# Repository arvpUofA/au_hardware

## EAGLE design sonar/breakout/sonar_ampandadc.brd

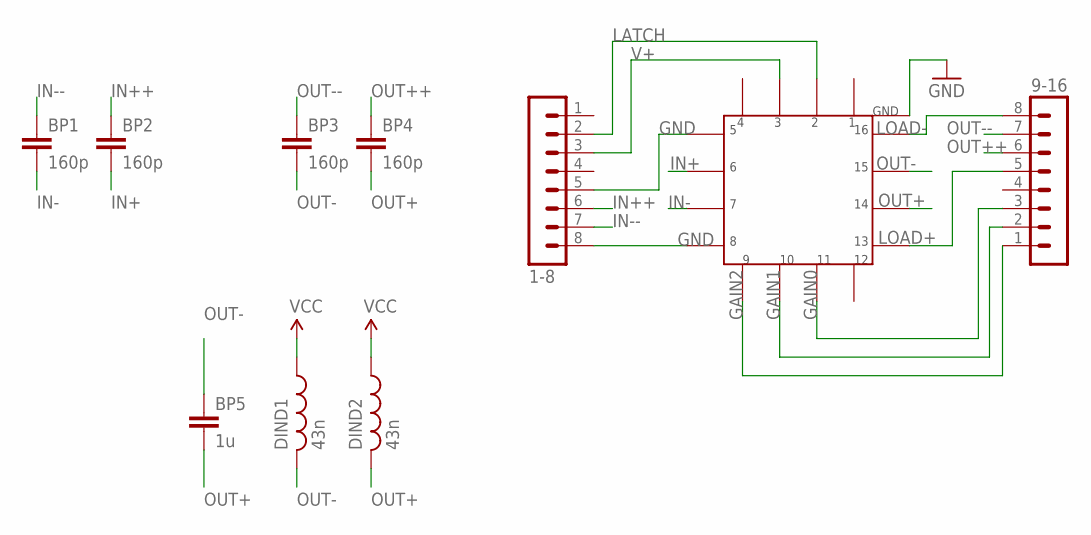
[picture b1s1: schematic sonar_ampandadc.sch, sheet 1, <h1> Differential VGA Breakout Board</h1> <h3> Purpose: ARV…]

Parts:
1-8, 9-16: MA08-1
BP1, BP2, BP3, BP4: 160p; 0603-CAP
BP5: 1u; 0603-CAP
DIND1, DIND2: 43n; 0402-RES
U$1: LMH6514; WQFN4X4

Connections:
GAIN0: 9-16.3, U$1.P$11
GAIN1: 9-16.2, U$1.P$10
GAIN2: 9-16.1, U$1.P$9
GND: 1-8.5, 1-8.8, U$1.GND, U$1.P$5, U$1.P$8; also elsewhere on the board
IN+: BP2.2, U$1.P$6
IN++: 1-8.6, BP2.1
IN-: BP1.2, U$1.P$7
IN--: 1-8.7, BP1.1
LATCH: 1-8.2, U$1.P$2
LOAD+: 9-16.5, U$1.P$13; also elsewhere on the board
LOAD-: 9-16.8, U$1.P$16; also elsewhere on the board
OUT+: BP4.2, BP5.2, DIND2.2, U$1.P$14
OUT++: 9-16.6, BP4.1; also elsewhere on the board
OUT-: BP3.2, BP5.1, DIND1.2, U$1.P$15
OUT--: 9-16.7, BP3.1; also elsewhere on the board
V+: 1-8.3, DIND1.1, DIND2.1, U$1.P$3; also elsewhere on the board

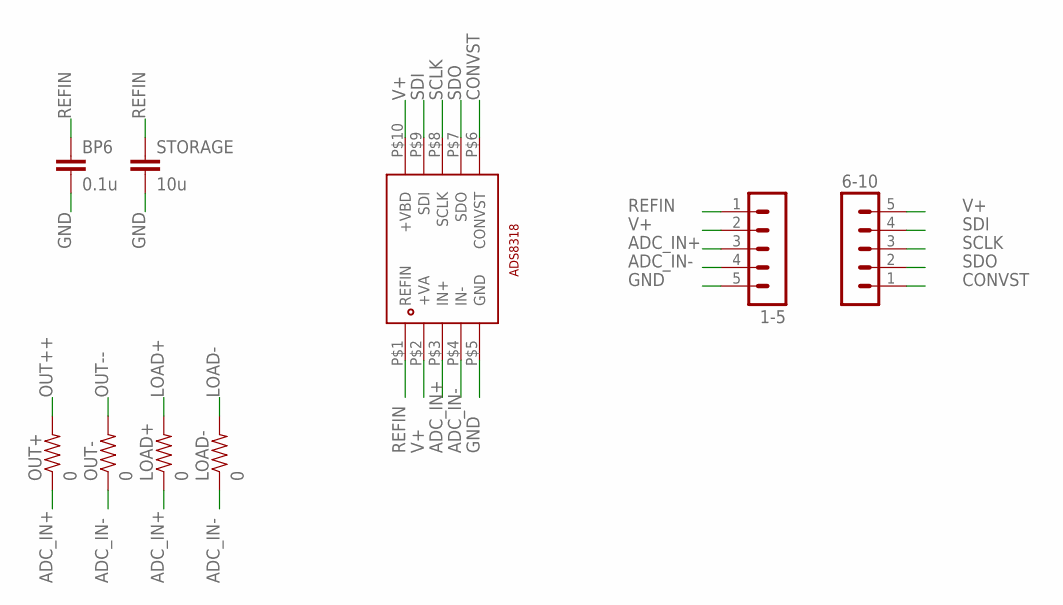
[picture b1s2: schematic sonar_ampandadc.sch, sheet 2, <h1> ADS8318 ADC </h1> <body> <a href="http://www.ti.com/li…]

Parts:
1-5, 6-10: MA05-1
BP6: 0.1u; 0603-CAP
LOAD+: 0; 0603-RES
LOAD-: 0; 0603-RES
OUT+: 0; 0603-RES
OUT-: 0; 0603-RES
STORAGE: 10u; 0603-CAP
U$2: ADS8318; 10-VSSOP

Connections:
ADC_IN+: 1-5.3, LOAD+.1, OUT+.1, U$2.P$3 (IN+)
ADC_IN-: 1-5.4, LOAD-.1, OUT-.1, U$2.P$4 (IN-)
CONVST: 6-10.1, U$2.P$6 (CONVST)
GND: 1-5.5, BP6.2, STORAGE.2, U$2.P$5 (GND); also elsewhere on the board
LOAD+: LOAD+.2; also elsewhere on the board
LOAD-: LOAD-.2; also elsewhere on the board
OUT++: OUT+.2; also elsewhere on the board
OUT--: OUT-.2; also elsewhere on the board
REFIN: 1-5.1, BP6.1, STORAGE.1, U$2.P$1 (REFIN)
SCLK: 6-10.3, U$2.P$8 (SCLK)
SDI: 6-10.4, U$2.P$9 (SDI)
SDO: 6-10.2, U$2.P$7 (SDO)
V+: 1-5.2, 6-10.5, U$2.P$2 (+VA), U$2.P$10 (+VBD); also elsewhere on the board

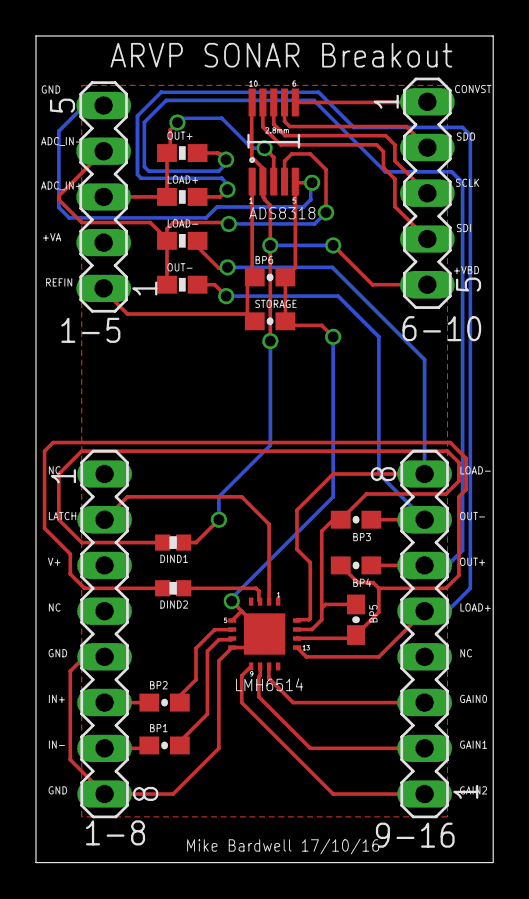
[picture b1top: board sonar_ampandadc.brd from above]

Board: 2 copper layers, 25.4 x 45.9 mm, 19 parts (0 on the bottom side), 23 nets.

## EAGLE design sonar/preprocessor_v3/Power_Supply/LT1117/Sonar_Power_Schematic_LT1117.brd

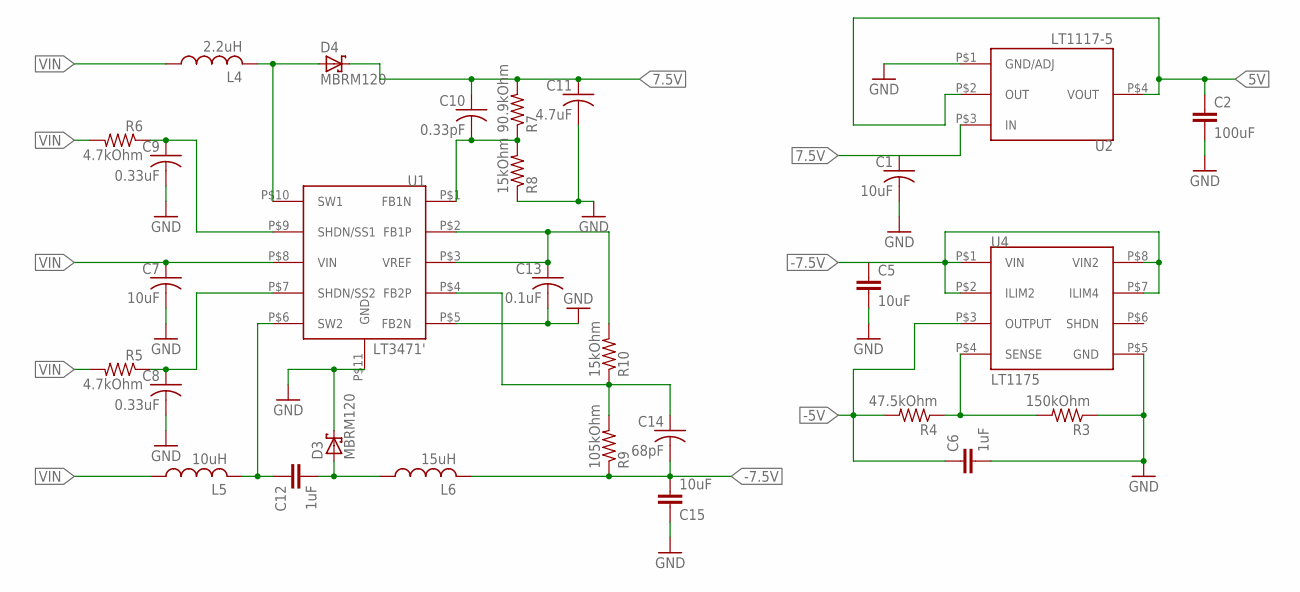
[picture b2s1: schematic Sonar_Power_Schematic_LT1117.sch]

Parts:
C1, C5, C7, C15: 10uF; C0603
C2: 100uF; C1210
C6, C12: 1uF; C1206
C8, C9: 0.33uF; C0603
C10: 0.33pF; C0603
C11: 4.7uF; C0603
C13: 0.1uF; C0603
C14: 68pF; C0603
D3, D4: MBRM120; DO-216AA
L4: 2.2uH; NS4.9X4.9
L5: 10uH; NS5X5
L6: 15uH; NS5X5
R3: 150kOhm; R0603
R4: 47.5kOhm; R0603
R5, R6: 4.7kOhm; R0603
R7: 90.9kOhm; R0603
R8, R10: 15kOhm; R0603
R9: 105kOhm; R0603
U1: LT3471'; 10-WFDFN
U2: LT1117-5; SOT233-3
U4: LT1175; 8-SOIC

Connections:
5V: C2.1, U2.P$2 (OUT), U2.P$4 (VOUT)
7.5V: C1.1, C10.1, C11.1, D4.P$1 (C), R7.2, U2.P$3 (IN)
-5V: C6.1, R4.2, U4.P$3 (OUTPUT)
-7.5V: C5.1, C14.2, C15.2, L6.P$2 (2), R9.1, U4.P$1 (VIN), U4.P$2 (ILIM2), U4.P$7 (ILIM4), U4.P$8 (VIN2)
GND: C1.2, C2.2, C5.2, C6.2, C7.2, C8.2, C9.2, C11.2, C13.2, C15.1, D3.P$1 (C), R3.1, R8.1, U1.P$5 (FB2N), U1.P$11 (GND), U2.P$1 (GND/ADJ), U4.P$5 (GND)
unnamed: R3.2, R4.1, U4.P$4 (SENSE)
unnamed: D4.P$2 (A), L4.P$2 (2), U1.P$10 (SW1)
unnamed: C10.2, R7.1, R8.2, U1.P$1 (FB1N)
unnamed: C12.1, L5.P$2 (2), U1.P$6 (SW2)
unnamed: C12.2, D3.P$2 (A), L6.P$1 (1)
unnamed: C14.1, R9.2, R10.1, U1.P$4 (FB2P)
SS1: C9.1, R6.1, U1.P$9 (SHDN/SS1)
SS2: C8.1, R5.1, U1.P$7 (SHDN/SS2)
VIN: C7.1, L4.P$1 (1), L5.P$1 (1), R5.2, R6.2, U1.P$8 (VIN)
VREF: C13.1, R10.2, U1.P$2 (FB1P), U1.P$3 (VREF)

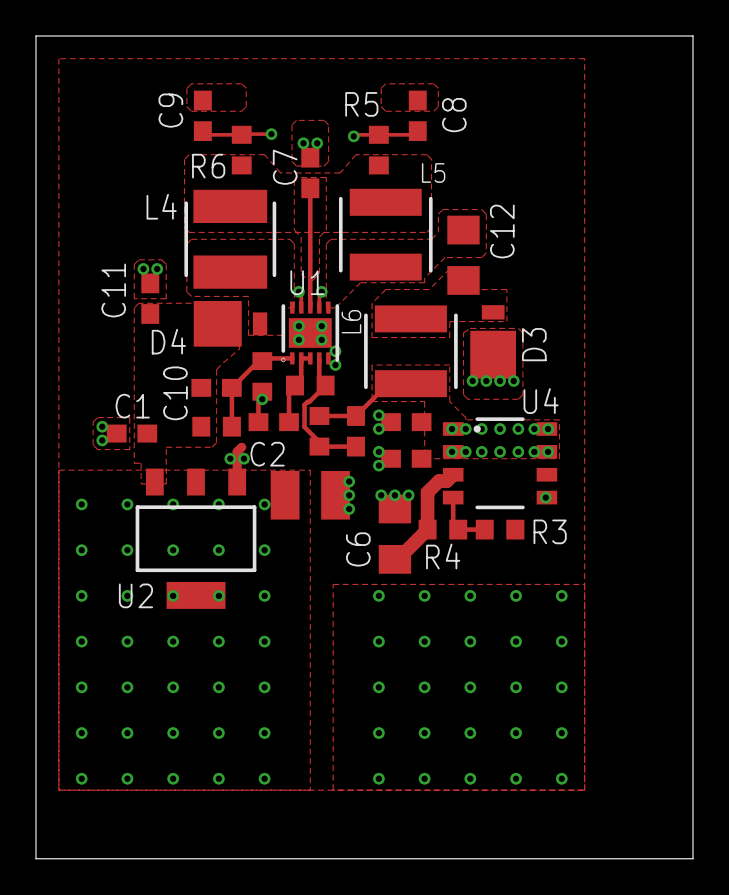
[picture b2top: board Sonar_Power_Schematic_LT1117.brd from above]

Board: 4 copper layers, 36.5 x 45.7 mm, 29 parts (0 on the bottom side), 15 nets.

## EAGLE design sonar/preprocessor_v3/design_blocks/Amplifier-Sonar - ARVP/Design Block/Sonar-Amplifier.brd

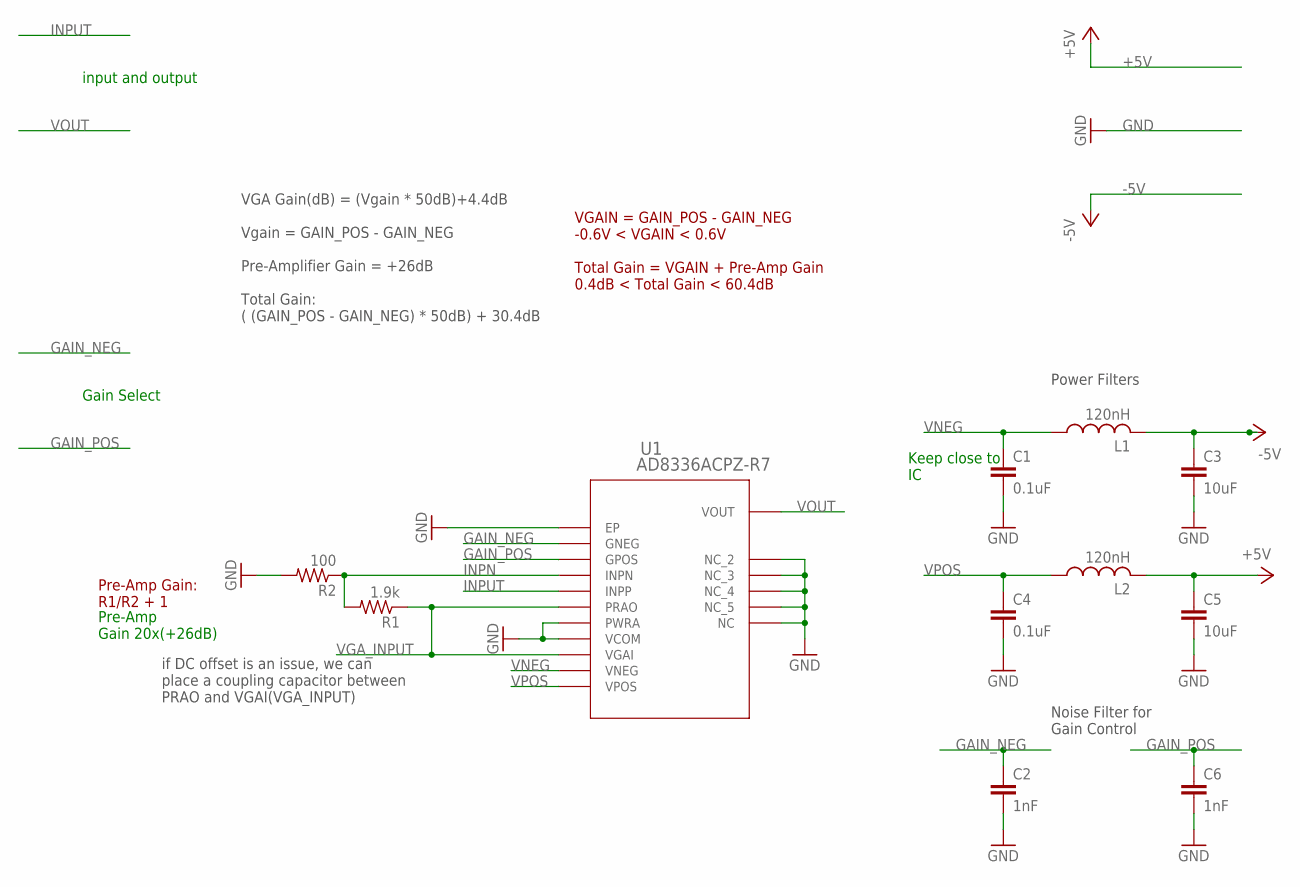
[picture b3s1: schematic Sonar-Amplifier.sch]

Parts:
C1, C4: 0.1uF; C0603
C2, C6: 1nF; C0603
C3, C5: 10uF; C1206
L1, L2: 120nH; L3225P
R1: 1.9k; R0603
R2: 100; R0603
U1: AD8336ACPZ-R7; CP_16_4

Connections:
+5V: C5.1, L2.2
-5V: C3.1, L1.2
GAIN_NEG: C2.1, U1.GNEG
GAIN_POS: C6.1, U1.GPOS
GND: C1.2, C2.2, C3.2, C4.2, C5.2, C6.2, R2.2, U1.GND1 (EP), U1.NC, U1.NC1 (NC_2), U1.NC2 (NC_3), U1.NC3 (NC_4), U1.NC4 (NC_5), U1.PWRA, U1.VCOM
INPN: R1.2, R2.1, U1.INPN
INPUT: U1.INPP
VGA_INPUT: R1.1, U1.PRAO, U1.VGAI
VNEG: C1.1, L1.1, U1.VNEG
VOUT: U1.VOUT
VPOS: C4.1, L2.1, U1.VPOS

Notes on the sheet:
Pre-Amp Gain 20x(+26dB)
Power Filters
Keep close to IC
Noise Filter for Gain Control
input and output
Pre-Amp Gain: R1/R2 + 1
if DC offset is an issue, we can place a coupling capacitor between PRAO and VGAI(VGA_INPUT)
Gain Select
VGA Gain(dB) = (Vgain * 50dB)+4.4dB Vgain = GAIN_POS - GAIN_NEG Pre-Amplifier Gain = +26dB Total Gain: ( (GAIN_POS - GAIN_NEG) * 50dB) + 30.4dB
VGAIN = GAIN_POS - GAIN_NEG -0.6V < VGAIN < 0.6V Total Gain = VGAIN + Pre-Amp Gain 0.4dB < Total Gain < 60.4dB

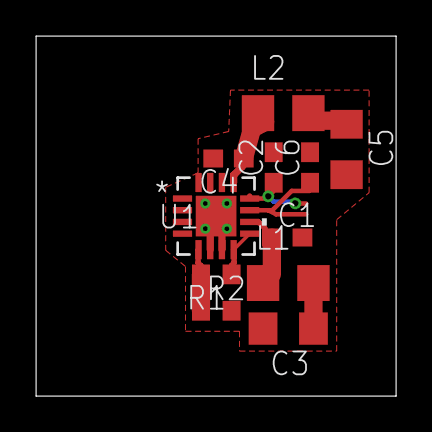
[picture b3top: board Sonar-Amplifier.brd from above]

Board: 4 copper layers, 20.0 x 20.0 mm, 11 parts (0 on the bottom side), 9 nets.

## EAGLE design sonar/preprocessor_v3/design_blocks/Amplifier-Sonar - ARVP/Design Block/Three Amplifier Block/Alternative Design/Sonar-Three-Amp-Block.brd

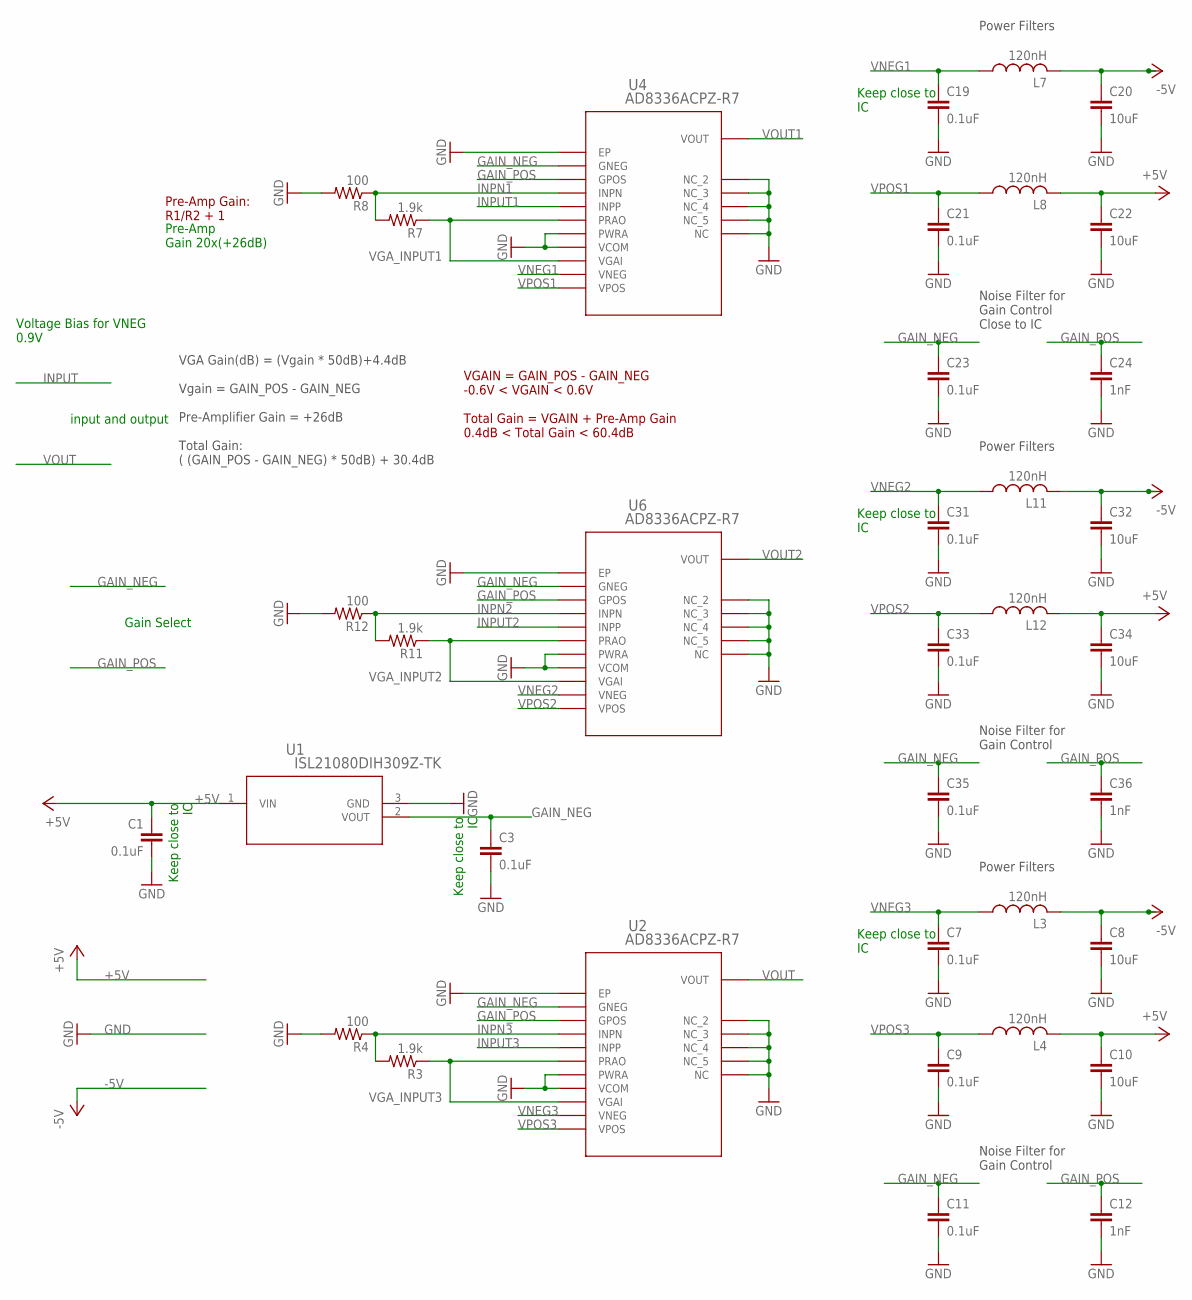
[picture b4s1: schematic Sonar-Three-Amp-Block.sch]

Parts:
C1, C3, C7, C9, C11, C19, C21, C23, C31, C33, C35: 0.1uF; C0603
C8, C10, C20, C22, C32, C34: 10uF; C1206
C12, C24, C36: 1nF; C0603
L3, L4, L7, L8, L11, L12: 120nH; L3225P
R3, R7, R11: 1.9k; R0603
R4, R8, R12: 100; R0603
U1: ISL21080DIH309Z-TK; P3_064
U2, U4, U6: AD8336ACPZ-R7; CP_16_4

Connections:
+5V: C1.1, C10.1, C22.1, C34.1, L4.2, L8.2, L12.2, U1.1 (VIN)
-5V: C8.1, C20.1, C32.1, L3.2, L7.2, L11.2
GAIN_NEG: C3.1, C11.1, C23.1, C35.1, U1.2 (VOUT), U2.GNEG, U4.GNEG, U6.GNEG
GAIN_POS: C12.1, C24.1, C36.1, U2.GPOS, U4.GPOS, U6.GPOS
GND: C1.2, C3.2, C7.2, C8.2, C9.2, C10.2, C11.2, C12.2, C19.2, C20.2, C21.2, C22.2, C23.2, C24.2, C31.2, C32.2, C33.2, C34.2, C35.2, C36.2, R4.2, R8.2, R12.2, U1.3 (GND), U2.GND1 (EP), U2.NC, U2.NC1 (NC_2), U2.NC2 (NC_3), U2.NC3 (NC_4), U2.NC4 (NC_5), U2.PWRA, U2.VCOM, U4.GND1 (EP), U4.NC, U4.NC1 (NC_2), U4.NC2 (NC_3), U4.NC3 (NC_4), U4.NC4 (NC_5), U4.PWRA, U4.VCOM, U6.GND1 (EP), U6.NC, U6.NC1 (NC_2), U6.NC2 (NC_3), U6.NC3 (NC_4), U6.NC4 (NC_5), U6.PWRA, U6.VCOM
INPN1: R7.2, R8.1, U4.INPN
INPN2: R11.2, R12.1, U6.INPN
INPN3: R3.2, R4.1, U2.INPN
INPUT1: U4.INPP
INPUT2: U6.INPP
INPUT3: U2.INPP
VGA_INPUT1: R7.1, U4.PRAO, U4.VGAI
VGA_INPUT2: R11.1, U6.PRAO, U6.VGAI
VGA_INPUT3: R3.1, U2.PRAO, U2.VGAI
VNEG1: C19.1, L7.1, U4.VNEG
VNEG2: C31.1, L11.1, U6.VNEG
VNEG3: C7.1, L3.1, U2.VNEG
VOUT: U2.VOUT
VOUT1: U4.VOUT
VOUT2: U6.VOUT
VPOS1: C21.1, L8.1, U4.VPOS
VPOS2: C33.1, L12.1, U6.VPOS
VPOS3: C9.1, L4.1, U2.VPOS

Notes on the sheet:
Pre-Amp Gain 20x(+26dB)
Power Filters
Keep close to IC
Noise Filter for Gain Control Close to IC
input and output
Pre-Amp Gain: R1/R2 + 1
Gain Select
VGA Gain(dB) = (Vgain * 50dB)+4.4dB Vgain = GAIN_POS - GAIN_NEG Pre-Amplifier Gain = +26dB Total Gain: ( (GAIN_POS - GAIN_NEG) * 50dB) + 30.4dB
VGAIN = GAIN_POS - GAIN_NEG -0.6V < VGAIN < 0.6V Total Gain = VGAIN + Pre-Amp Gain 0.4dB < Total Gain < 60.4dB
Noise Filter for Gain Control
Voltage Bias for VNEG 0.9V

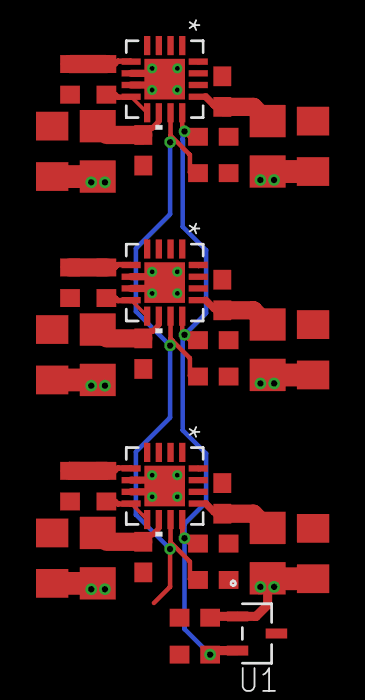
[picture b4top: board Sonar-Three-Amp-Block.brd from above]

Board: 4 copper layers, 36 parts (0 on the bottom side), 17 nets.

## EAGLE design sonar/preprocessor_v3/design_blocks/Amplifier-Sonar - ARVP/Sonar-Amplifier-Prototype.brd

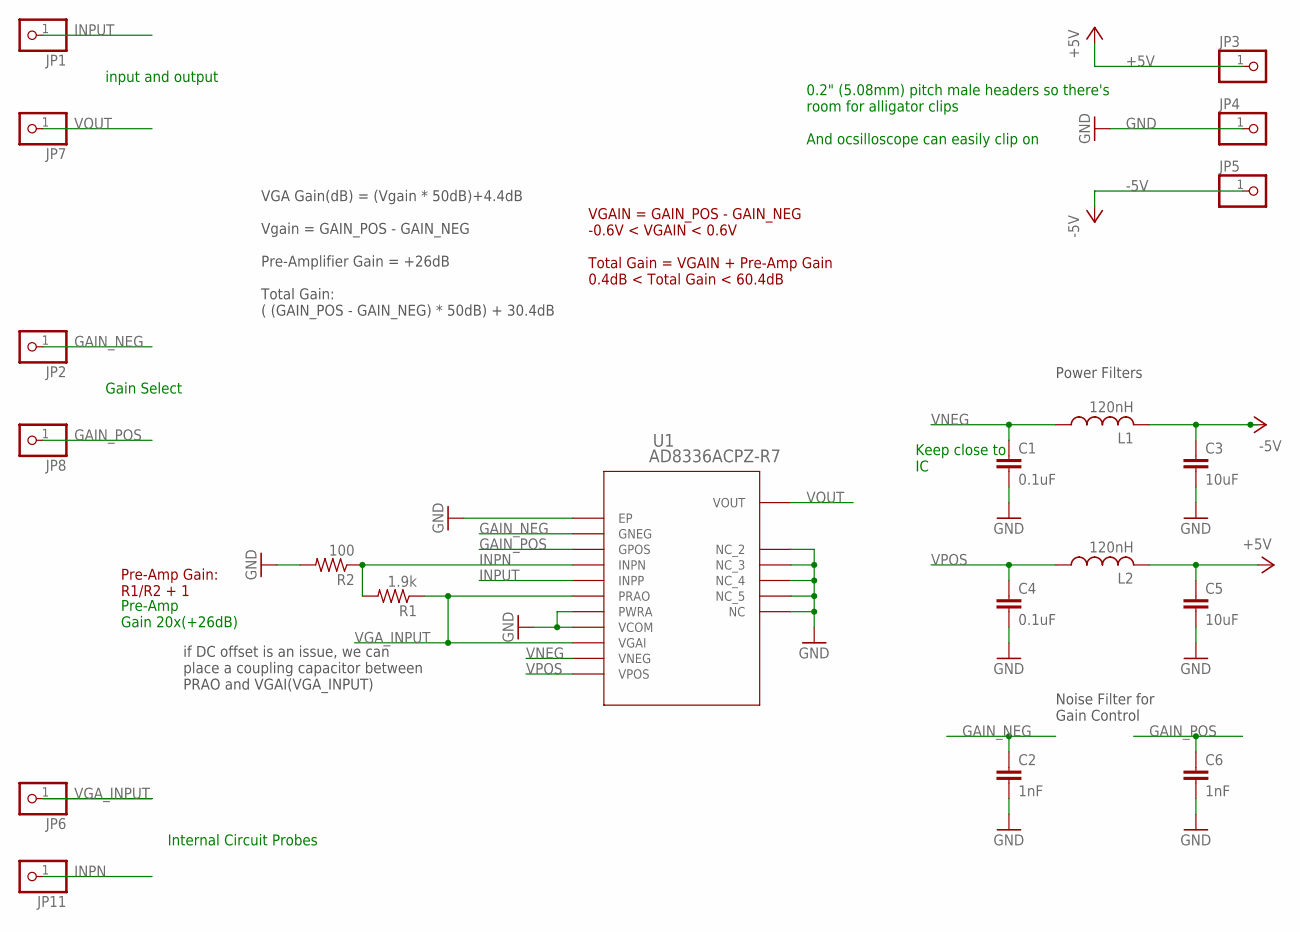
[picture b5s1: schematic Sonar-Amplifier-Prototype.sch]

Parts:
C1, C4: 0.1uF; C0603
C2, C6: 1nF; C0603
C3, C5: 10uF; C1206
JP1, JP2, JP3, JP4, JP5, JP6, JP7, JP8, JP11: PINHD-1X1; 1X01
L1, L2: 120nH; L3225P
R1: 1.9k; R0603
R2: 100; R0603
U1: AD8336ACPZ-R7; CP_16_4

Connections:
+5V: C5.1, JP3.1, L2.2
-5V: C3.1, JP5.1, L1.2
GAIN_NEG: C2.1, JP2.1, U1.GNEG
GAIN_POS: C6.1, JP8.1, U1.GPOS
GND: C1.2, C2.2, C3.2, C4.2, C5.2, C6.2, JP4.1, R2.2, U1.GND1 (EP), U1.NC, U1.NC1 (NC_2), U1.NC2 (NC_3), U1.NC3 (NC_4), U1.NC4 (NC_5), U1.PWRA, U1.VCOM
INPN: JP11.1, R1.2, R2.1, U1.INPN
INPUT: JP1.1, U1.INPP
VGA_INPUT: JP6.1, R1.1, U1.PRAO, U1.VGAI
VNEG: C1.1, L1.1, U1.VNEG
VOUT: JP7.1, U1.VOUT
VPOS: C4.1, L2.1, U1.VPOS

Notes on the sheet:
Pre-Amp Gain 20x(+26dB)
Power Filters
Keep close to IC
Noise Filter for Gain Control
0.2" (5.08mm) pitch male headers so there's room for alligator clips And ocsilloscope can easily clip on
input and output
Pre-Amp Gain: R1/R2 + 1
if DC offset is an issue, we can place a coupling capacitor between PRAO and VGAI(VGA_INPUT)
Gain Select
VGA Gain(dB) = (Vgain * 50dB)+4.4dB Vgain = GAIN_POS - GAIN_NEG Pre-Amplifier Gain = +26dB Total Gain: ( (GAIN_POS - GAIN_NEG) * 50dB) + 30.4dB
VGAIN = GAIN_POS - GAIN_NEG -0.6V < VGAIN < 0.6V Total Gain = VGAIN + Pre-Amp Gain 0.4dB < Total Gain < 60.4dB
Internal Circuit Probes

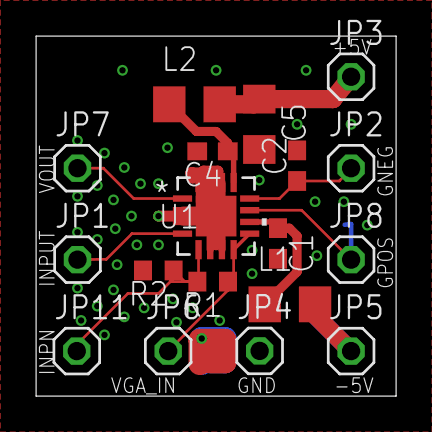
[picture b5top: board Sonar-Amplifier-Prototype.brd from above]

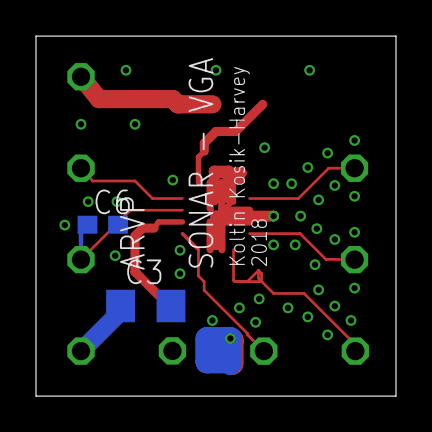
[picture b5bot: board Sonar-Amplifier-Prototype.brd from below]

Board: 2 copper layers, 20.0 x 20.0 mm, 20 parts (2 on the bottom side), 11 nets.

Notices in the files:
parts and their libraries:
SparkFun-Capacitors: Licensing: Creative Commons ShareAlike 4.0 International - https://creativecommons.org/licenses/by-sa/4.0
